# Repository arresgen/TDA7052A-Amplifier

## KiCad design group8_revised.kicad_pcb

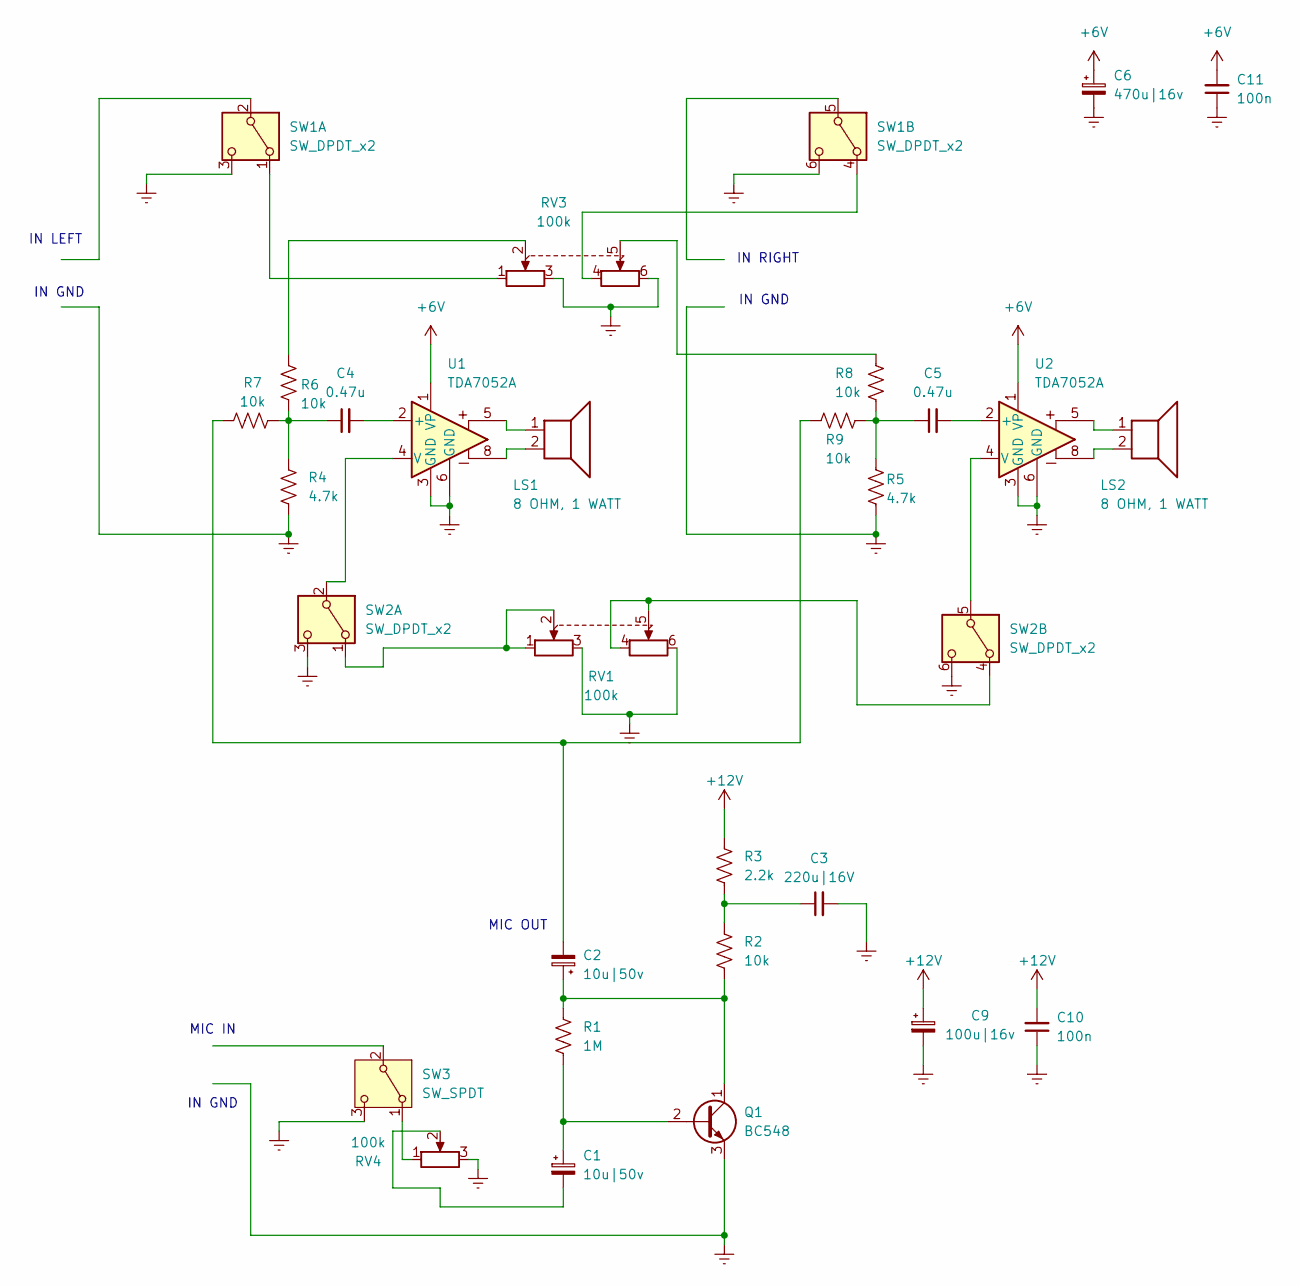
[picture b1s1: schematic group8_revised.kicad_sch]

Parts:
C1, C2: 10u|50v; CP_Radial_D8.0mm_P5.00mm
C3: 220u|16V; C_0201_0603Metric
C4, C5: 0.47u; C_0201_0603Metric
C6: 470u|16v; CP_Radial_D8.0mm_P3.80mm
C9: 100u|16v; CP_Radial_D8.0mm_P3.80mm
C10: 100n; C_Disc_D5.0mm_W2.5mm_P5.00mm
C11: 100n; C_0201_0603Metric
LS1: 8 OHM, 1 WATT; PinHeader_2x01_P1.00mm_Vertical
LS2: 8 OHM, 1 WATT; PinHeader_2x01_P2.00mm_Vertical_SMD
Q1: BC548; TO-92_Inline
R1: 1M; R_Axial_DIN0207_L6.3mm_D2.5mm_P7.62mm_Horizontal
R2, R7, R9: 10k; R_0603_1608Metric
R3: 2.2k; R_0603_1608Metric
R4: 4.7k; R_0603_1608Metric
R5: 4.7k; R_Axial_DIN0207_L6.3mm_D2.5mm_P7.62mm_Horizontal
R6, R8: 10k; R_Axial_DIN0207_L6.3mm_D2.5mm_P7.62mm_Horizontal
RV1, RV3: 100k; Potentiometer_Piher_PC-16_Dual_Horizontal
RV4: 100k; Potentiometer_Alps_RK09Y11_Single_Horizontal
SW1: SW_DPDT_x2; SW_CK_JS202011AQN_DPDT_Angled
SW2: SW_DPDT_x2; SW_CK_JS202011CQN_DPDT_Straight
SW3: SW_SPDT; SW_Slide_SPDT_Straight_CK_OS102011MS2Q
U1, U2: TDA7052A; SOIC-8_3.9x4.9mm_P1.27mm

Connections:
+6V: C6.1, C11.2, U1.1 (VP), U2.1 (VP)
+12V: C9.1, C10.2, R3.1
Earth: C3.2, C6.2, C9.2, C10.1, C11.1, Q1.3 (E), R4.2, R5.1, RV1.3, RV1.6, RV3.3, RV3.6, RV4.3, SW1.3 (C), SW1.6 (C), SW2.3 (C), SW2.6 (C), SW3.3 (C), U1.3 (GND), U1.6 (GND), U2.3 (GND), U2.6 (GND)
unnamed: C1.2, RV4.2
unnamed: C2.2, R7.1, R9.1
unnamed: C3.1, R2.1, R3.2
unnamed: C4.1, R4.1, R6.2, R7.2
unnamed: C5.1, R5.2, R8.2, R9.2
unnamed: LS1.1, U1.5
unnamed: LS1.2, U1.8
unnamed: LS2.1, U2.5
unnamed: LS2.2, U2.8
unnamed: C1.1, Q1.2 (B), R1.2
unnamed: C2.1, Q1.1 (C), R1.1, R2.2
unnamed: R6.1, RV3.2
unnamed: R8.1, RV3.5
unnamed: RV3.1, SW1.1 (A)
unnamed: RV3.4, SW1.4 (A)
unnamed: RV1.1, RV1.2, SW2.1 (A)
unnamed: SW2.2 (B), U1.4 (V)
unnamed: RV1.4, RV1.5, SW2.4 (A)
unnamed: SW2.5 (B), U2.4 (V)
unnamed: RV4.1, SW3.1 (A)
unnamed: C4.2, U1.2 (+)
unnamed: C5.2, U2.2 (+)

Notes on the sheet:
MIC IN
IN RIGHT
IN LEFT
IN GND
MIC OUT

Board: 2 copper layers, 29 parts (0 on the bottom side), 25 nets, no tracks yet.
